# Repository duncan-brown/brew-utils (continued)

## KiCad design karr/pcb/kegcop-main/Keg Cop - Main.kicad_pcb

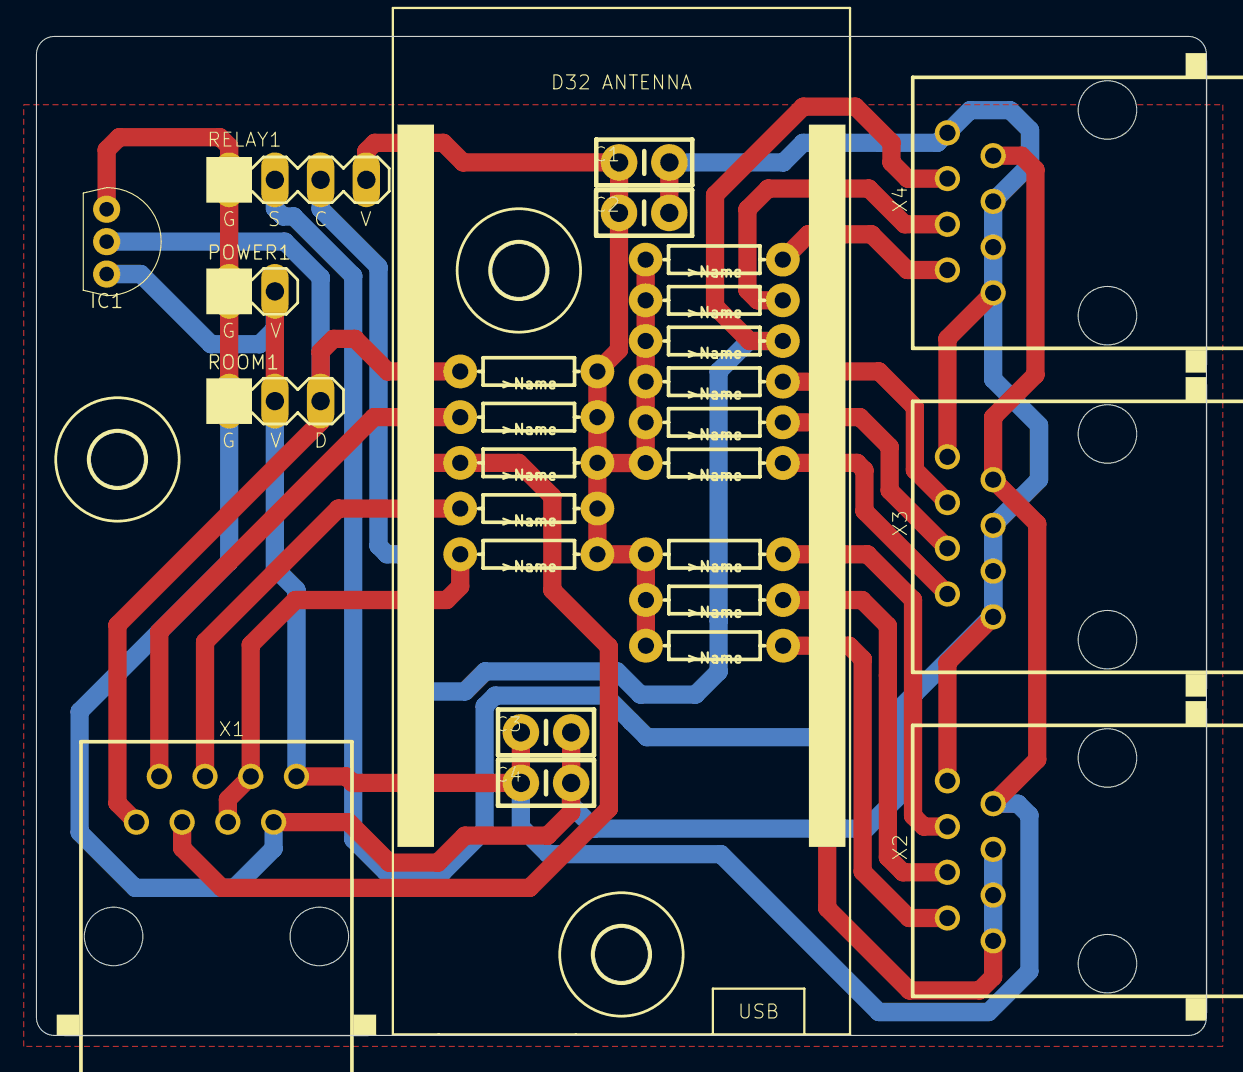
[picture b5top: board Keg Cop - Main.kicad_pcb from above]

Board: 2 copper layers, 65.0 x 55.5 mm, 30 parts (0 on the bottom side), 19 nets.

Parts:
C1, C3: 0.1μF; CAP_PTH-2.54
C2, C4: 1.0μF; CAP_PTH-2.54
D32: Lolin D32; D32_NO_BATT
IC1: DS18B20+; TO-92
POWER1: 2-PIN; HDR-2_VERT
R1, R2, R3, R4, R5, R6, R7, R8, R9, R10, R11, R12, R13, R14: 2.2kΩ; AXIAL-0.3
RELAY1: 4-PIN; MA04-1
ROOM1: 3-PIN; HDR-3_VERT
U$1, U$2, U$3: 3,0
X1, X2, X3, X4: RJ45; RJ45-NO-SHIELD

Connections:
/3V3: C1.1, C2.1, D32.VCC, R1.P$1, R2.P$1, R3.P$1, R4.P$1, R5.P$1, R6.P$2, R7.P$2, R8.P$2, R9.P$2, R10.P$2, R11.P$2, R12.P$2, R13.P$2, R14.P$2, RELAY1.4
/5V: C3.1, C4.1, D32.VBUS, IC1.3, POWER1.2, ROOM1.2, X1.8, X2.7, X3.7, X4.7
/COOL: D32.IO27, RELAY1.3
/GND: C1.2, C2.2, C3.2, C4.2, D32.GND, D32.GND2, IC1.1, POWER1.1, RELAY1.1, ROOM1.1, X1.7, X2.1, X2.3, X2.5, X2.8, X3.1, X3.3, X3.5, X3.8, X4.1, X4.3, X4.5, X4.8
/KDAT: D32.IO14, R5.P$2, X1.5, X1.6
/KEG0: D32.IO4, R14.P$1, X2.2
/KEG1: D32.IO16, R13.P$1, X2.4
/KEG2: D32.IO17, R12.P$1, X2.6
/KEG3: D32.IO18, R11.P$1, X3.2
/KEG4: D32.IO19, R10.P$1, X3.4
/KEG5: D32.IO21, R9.P$1, X3.6
/KEG6: D32.IO22, R8.P$1, X4.2
/KEG7: D32.IO23, R7.P$1, X4.4
/KEG8: D32.IO13, R6.P$1, X4.6
/LDAT: D32.IO26, R4.P$2, X1.4
/RDAT: D32.IO32, IC1.2, R1.P$2, ROOM1.3, X1.1
/SOL: D32.IO2, RELAY1.2
/TDAT: D32.IO33, R2.P$2, X1.2
/UDAT: D32.IO25, R3.P$2, X1.3

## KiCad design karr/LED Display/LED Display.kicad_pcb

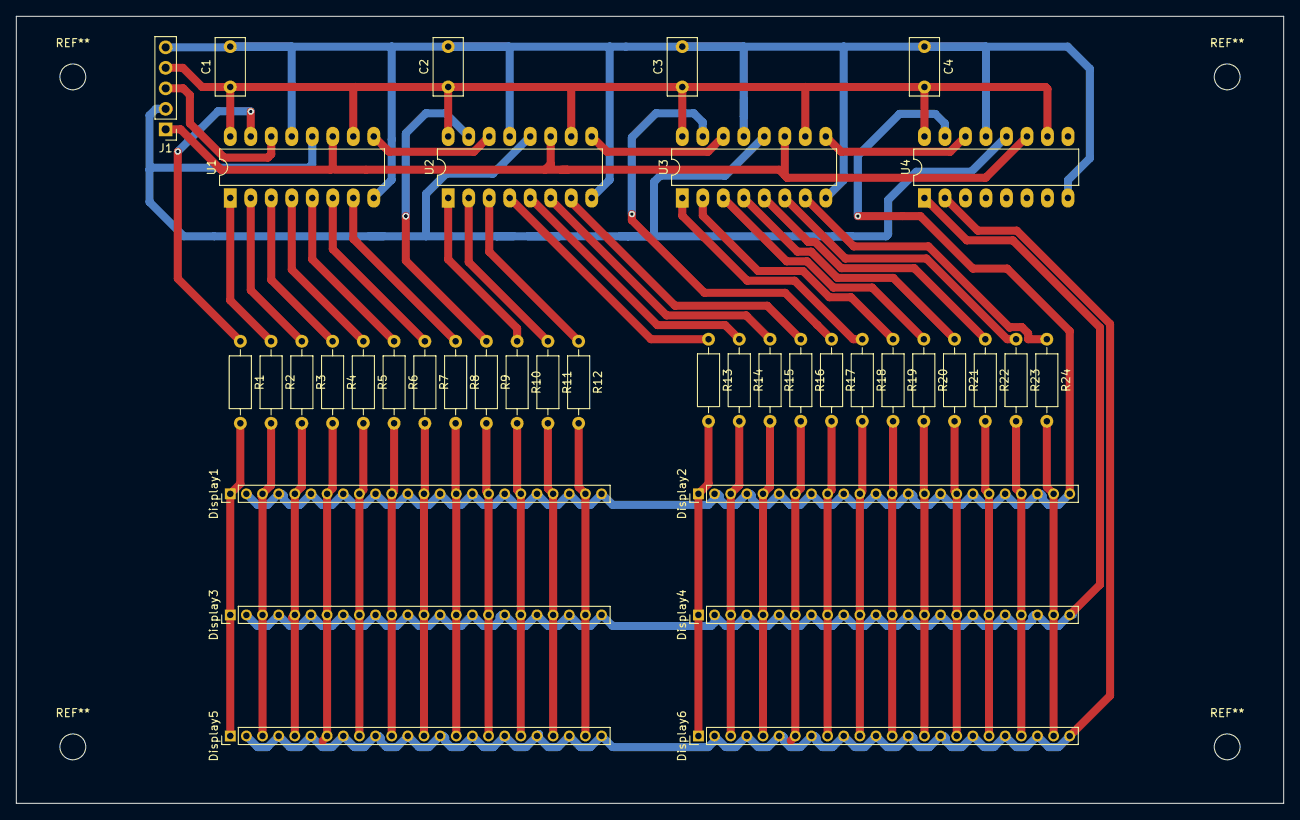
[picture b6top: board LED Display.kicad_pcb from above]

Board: 2 copper layers, 157.0 x 97.5 mm, 39 parts (0 on the bottom side), 59 nets.

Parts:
C1, C2, C3, C4: 100nF; C_Rect_L7.0mm_W3.5mm_P5.00mm
Display1, Display3, Display5: STBD001-4R8G; PinHeader_1x24_P2.00mm_Vertical
Display2, Display4, Display6: KYX-125807R; PinHeader_1x24_P2.00mm_Vertical
J1: Conn_01x05; PinHeader_1x05_P2.54mm_Vertical
R1, R2, R3, R4, R13, R14, R15, R16, R17, R18, R19, R20, R21, R22, R23, R24: 2k2; R_Axial_DIN0207_L6.3mm_D2.5mm_P10.16mm_Horizontal
R5, R6, R7, R8, R9, R10, R11, R12: 680R; R_Axial_DIN0207_L6.3mm_D2.5mm_P10.16mm_Horizontal
U1, U2, U3, U4: 74HC595; DIP-16_W7.62mm_LongPads

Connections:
+5V: C1.1, C2.1, C3.1, C4.2, J1.4, U1.10, U1.16, U2.10, U2.16, U3.10, U3.16, U4.10, U4.16
GND: C1.2, C2.2, C3.2, C4.1, J1.5, U1.8, U1.13, U2.8, U2.13, U3.8, U3.13, U4.8, U4.13
unnamed: Display1.1, Display3.1, Display5.1, R1.2
unnamed: Display1.3, Display3.3, Display5.3, R2.2
unnamed: Display1.5, Display3.5, Display5.5, R3.2
unnamed: Display1.7, Display3.7, Display5.7, R4.2
unnamed: Display1.9, Display3.9, Display5.9, R5.2
unnamed: Display1.2, Display1.4, Display1.6, Display1.8, Display1.10, Display1.12, Display1.14, Display1.16, Display1.18, Display1.20, Display1.22, Display1.24, Display2.2, Display2.4, Display2.6, Display2.8, Display2.10, Display2.12, Display2.14, Display2.16, Display2.18, Display2.20, Display2.22, Display2.24, U4.15
unnamed: Display1.11, Display3.11, Display5.11, R6.2
unnamed: Display1.13, Display3.13, Display5.13, R7.2
unnamed: Display1.15, Display3.15, Display5.15, R8.2
unnamed: Display1.17, Display3.17, Display5.17, R9.2
unnamed: Display1.19, Display3.19, Display5.19, R10.2
unnamed: Display1.21, Display3.21, Display5.21, R11.2
unnamed: Display1.23, Display3.23, Display5.23, R12.2
unnamed: Display2.1, Display4.1, Display6.1, R13.2
unnamed: Display2.3, Display4.3, Display6.3, R14.2
unnamed: Display2.5, Display4.5, Display6.5, R15.2
unnamed: Display2.7, Display4.7, Display6.7, R16.2
unnamed: Display2.9, Display4.9, Display6.9, R17.2
unnamed: Display2.11, Display4.11, Display6.11, R18.2
unnamed: Display2.13, Display4.13, Display6.13, R19.2
unnamed: Display2.15, Display4.15, Display6.15, R20.2
unnamed: Display2.17, Display4.17, Display6.17, R21.2
unnamed: Display2.19, Display4.19, Display6.19, R22.2
unnamed: Display2.21, Display4.21, Display6.21, R23.2
unnamed: Display2.23, Display4.23, Display6.23, R24.2
unnamed: Display3.2, Display3.4, Display3.6, Display3.8, Display3.10, Display3.12, Display3.14, Display3.16, Display3.18, Display3.20, Display3.22, Display3.24, Display4.2, Display4.4, Display4.6, Display4.8, Display4.10, Display4.12, Display4.14, Display4.16, Display4.18, Display4.20, Display4.22, Display4.24, U4.1
unnamed: Display5.2, Display5.4, Display5.6, Display5.8, Display5.10, Display5.12, Display5.14, Display5.16, Display5.18, Display5.20, Display5.22, Display5.24, Display6.2, Display6.4, Display6.6, Display6.8, Display6.10, Display6.12, Display6.14, Display6.16, Display6.18, Display6.20, Display6.22, Display6.24, U4.2
unnamed: J1.1, U1.11, U2.11, U3.11, U4.11
unnamed: J1.2, U1.12, U2.12, U3.12, U4.12
unnamed: J1.3, U1.14
unnamed: R1.1, U1.15
unnamed: R2.1, U1.1
unnamed: R3.1, U1.2
unnamed: R4.1, U1.3
unnamed: R5.1, U1.4
unnamed: R6.1, U1.5
unnamed: R7.1, U1.6
unnamed: R8.1, U1.7
unnamed: R9.1, U2.15
unnamed: R10.1, U2.1
unnamed: R11.1, U2.2
unnamed: R12.1, U2.3
unnamed: R13.1, U2.4
unnamed: R14.1, U2.5
unnamed: R15.1, U2.6
unnamed: R16.1, U2.7
unnamed: R17.1, U3.15
unnamed: R18.1, U3.1
unnamed: R19.1, U3.2
unnamed: R20.1, U3.3
unnamed: R21.1, U3.4
unnamed: R22.1, U3.5
unnamed: R23.1, U3.6
unnamed: R24.1, U3.7
unnamed: U1.9, U2.14
unnamed: U2.9, U3.14
unnamed: U3.9, U4.14

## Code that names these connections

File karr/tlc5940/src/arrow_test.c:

#include <stdio.h>
#include <stdlib.h>
#include <string.h>

#include "arrow_test.h"

#include "freertos/FreeRTOS.h"
#include "freertos/task.h"
#include "esp_err.h"
#include "esp_log.h"

#include "st7789.h"
#include "fontx.h"

extern uint16_t segment_0;
extern uint16_t bar;

TickType_t DisplaySegment0(TFT_t * dev, FontxFile *fx, int width, int height) {
	TickType_t startTick, endTick, diffTick;
	startTick = xTaskGetTickCount();

	// get font width & height
	uint8_t buffer[FontxGlyphBufSize];
	uint8_t fontWidth;
	uint8_t fontHeight;
	GetFontx(fx, 0, buffer, &fontWidth, &fontHeight);
	//ESP_LOGI(__FUNCTION__,"fontWidth=%d fontHeight=%d",fontWidth,fontHeight);
	
	uint16_t xpos;
	uint16_t ypos;
	const uint8_t ascii_len = 28;
	uint8_t ascii[ascii_len];
	uint16_t color;

	lcdFillScreen(dev, BLACK);
	lcdSetFontDirection(dev, DIRECTION90);
	color = WHITE;
	ypos = 0;
    xpos = width - 1;

    snprintf((char *)ascii, ascii_len, "%d (%d)", segment_0, bar);
	xpos -= fontHeight + 1;
	lcdDrawString(dev, fx, xpos, ypos, ascii, color);

	endTick = xTaskGetTickCount();
	diffTick = endTick - startTick;
	ESP_LOGI(__FUNCTION__, "elapsed time[ms]:%d",diffTick*portTICK_RATE_MS);
	return diffTick;
}

TickType_t DisplayTLCPins(TFT_t * dev, FontxFile *fx, int width, int height) {
	TickType_t startTick, endTick, diffTick;
	startTick = xTaskGetTickCount();

	// get font width & height
	uint8_t buffer[FontxGlyphBufSize];
	uint8_t fontWidth;
	uint8_t fontHeight;
	GetFontx(fx, 0, buffer, &fontWidth, &fontHeight);
	//ESP_LOGI(__FUNCTION__,"fontWidth=%d fontHeight=%d",fontWidth,fontHeight);
	
	uint16_t xpos;
	uint16_t ypos;
	const uint8_t ascii_len = 28;
	uint8_t ascii[ascii_len];
	uint16_t color;

	lcdFillScreen(dev, BLACK);
	lcdSetFontDirection(dev, DIRECTION90);
	color = WHITE;
	ypos = 0;
    xpos = width - 1;

    snprintf((char *)ascii, ascii_len, "    SIN: %d   VPRG: %d", CONFIG_TLC_SIN_PIN, CONFIG_TLC_VPRG_PIN);
	xpos -= fontHeight + 1;
	lcdDrawString(dev, fx, xpos, ypos, ascii, color);

	snprintf((char *)ascii, ascii_len, "   SOUT: %d   XLAT: %d", CONFIG_TLC_SOUT_PIN, CONFIG_TLC_XLAT_PIN);
	xpos -= fontHeight + 1;
	lcdDrawString(dev, fx, xpos, ypos, ascii, color);

	snprintf((char *)ascii, ascii_len, "   SCLK: %d  BLANK: %d", CONFIG_TLC_SCLK_PIN, CONFIG_TLC_BLANK_PIN);
	xpos -= fontHeight + 1;
	lcdDrawString(dev, fx, xpos, ypos, ascii, color);

	snprintf((char *)ascii, ascii_len, "  DCPRG: %d  GSCLK: %d", CONFIG_TLC_DCPRG_PIN, CONFIG_TLC_GSCLK_PIN);
	xpos -= fontHeight + 1;
	lcdDrawString(dev, fx, xpos, ypos, ascii, color);

	snprintf((char *)ascii, ascii_len, "COUNTER: %d  LINE 1: %d", CONFIG_TLC_COUNTER_PIN, CONFIG_TLC_LINE_1_PIN);
	xpos -= fontHeight + 1;
	lcdDrawString(dev, fx, xpos, ypos, ascii, color);

	snprintf((char *)ascii, ascii_len, "  LINE2: %d  LINE 3: %d", CONFIG_TLC_LINE_2_PIN, CONFIG_TLC_LINE_3_PIN);
	xpos -= fontHeight + 1;
	lcdDrawString(dev, fx, xpos, ypos, ascii, color);

	endTick = xTaskGetTickCount();
	diffTick = endTick - startTick;
	ESP_LOGI(__FUNCTION__, "elapsed time[ms]:%d",diffTick*portTICK_RATE_MS);
	return diffTick;
}

TickType_t ArrowTest(TFT_t * dev, FontxFile *fx, int width, int height) {
	TickType_t startTick, endTick, diffTick;
	startTick = xTaskGetTickCount();

	// get font width & height
	uint8_t buffer[FontxGlyphBufSize];
	uint8_t fontWidth;
	uint8_t fontHeight;
	GetFontx(fx, 0, buffer, &fontWidth, &fontHeight);
	//ESP_LOGI(__FUNCTION__,"fontWidth=%d fontHeight=%d",fontWidth,fontHeight);
	
	uint16_t xpos;
	uint16_t ypos;
	int	stlen;
	uint8_t ascii[24];
	uint16_t color;

	lcdFillScreen(dev, BLACK);

	strcpy((char *)ascii, "KARR");
	if (width < height) {
		xpos = ((width - fontHeight) / 2) - 1;
		ypos = (height - (strlen((char *)ascii) * fontWidth)) / 2;
		lcdSetFontDirection(dev, DIRECTION90);
	} else {
		ypos = ((height - fontHeight) / 2) - 1;
		xpos = (width - (strlen((char *)ascii) * fontWidth)) / 2;
		lcdSetFontDirection(dev, DIRECTION0);
	}
	color = WHITE;
	lcdDrawString(dev, fx, xpos, ypos, ascii, color);

	lcdSetFontDirection(dev, 0);
	color = RED;
	lcdDrawFillArrow(dev, 10, 10, 0, 0, 5, color);
	strcpy((char *)ascii, "0,0");
	lcdDrawString(dev, fx, 0, 30, ascii, color);

	color = GREEN;
	lcdDrawFillArrow(dev, width-11, 10, width-1, 0, 5, color);
	//strcpy((char *)ascii, "79,0");
	sprintf((char *)ascii, "%d,0",width-1);
	stlen = strlen((char *)ascii);
	xpos = (width-1) - (fontWidth*stlen);
	lcdDrawString(dev, fx, xpos, 30, ascii, color);

	color = GRAY;
	lcdDrawFillArrow(dev, 10, height-11, 0, height-1, 5, color);
	//strcpy((char *)ascii, "0,159");
	sprintf((char *)ascii, "0,%d",height-1);
	ypos = (height-11) - (fontHeight) + 5;
	lcdDrawString(dev, fx, 0, ypos, ascii, color);

	color = CYAN;
	lcdDrawFillArrow(dev, width-11, height-11, width-1, height-1, 5, color);
	//strcpy((char *)ascii, "79,159");
	sprintf((char *)ascii, "%d,%d",width-1, height-1);
	stlen = strlen((char *)ascii);
	xpos = (width-1) - (fontWidth*stlen);
	lcdDrawString(dev, fx, xpos, ypos, ascii, color);

	endTick = xTaskGetTickCount();
	diffTick = endTick - startTick;
	ESP_LOGI(__FUNCTION__, "elapsed time[ms]:%d",diffTick*portTICK_RATE_MS);
	return diffTick;
}

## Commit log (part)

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2020-08-01 cvs conversion program
2021-02-15 test program for 7-segment led
2021-02-16 fixed for correct segment pinout
2021-02-16 fixed loop
2021-02-16 include 9
2021-02-16 set all digits
2021-02-16 set ground pins and fix indentation
2021-02-16 update ground pins
2021-02-16 reduce flicker and break out digits
2021-02-16 move 20->16, 16->12
2021-02-16 don't blink dp
2021-02-16 reduce flicker
2021-02-16 removed redundant modulo test
2021-02-17 set up for low side switches
2021-02-17 test program using pigpen library
2021-02-17 pigpio based version
2021-02-17 decrease flicker
2021-02-17 add mash temp
2021-02-17 start mash temp thread
2021-02-17 fix mash probe name
2021-02-17 mash temp is a float
2021-02-17 remove decimal point from temp string
2021-02-17 fix mash temp formatting
2021-02-17 fix 6
2021-02-17 systemd service file
2021-02-19 update probe names for two buses
2021-02-19 update mash probe id
2021-02-20 remove duplicate import
2021-02-20 simple program to print temperature and time
2021-02-20 print time in minutes
2021-02-27 try to fix crash
    https://raspberrypi.stackexchange.com/questions/61621/sending-new-wave-to-pigpiod-causes-pi-to-lock-up
2021-02-28 avoid crash and blink
2021-02-28 fix typo
2021-03-14 added kicad files for led display
2021-04-11 add all 6 keezer probes
2021-07-24 rewire pins
2021-07-24 rewire again
2021-07-24 add hlt probe
2021-07-24 typo
2021-07-24 update probe ids
2021-08-06 rename prototypes
2021-08-06 original version from lbussy
2021-08-06 initial entry
2021-08-06 group outline
2021-08-07 inital entry
2021-08-07 removed pdf
2021-08-08 https://github.com/Xinyuan-LilyGO/TTGO-T-Display/issues/28#issuecomment-619570440
2021-08-08 switch to https://github.com/BravoRoot/ttgo-tdisplay-kicad
2021-08-08 from https://github.com/BravoRoot/ttgo-tdisplay-kicad
2021-08-08 ttgo plus seven chips
2021-08-08 based on mph
2021-08-08 fixed labels
2021-08-08 removed old file
2021-08-08 cloned with https://github.com/bobc/KiRename
2021-08-08 first four 7-segment displays
2021-08-08 store all libraries in project
2021-08-08 wire up a-f on displays
2021-08-08 created footpad for 7-segment
2021-08-08 added symbols
2021-08-08 fixed footpads
2021-08-08 add coupling capacitors
2021-08-08 fixed missing footpads
2021-08-08 added datasheets
2021-08-08 switch regulator
2021-08-08 finished wiring
2021-08-08 reworked pins
2021-08-08 added mph leds
2021-08-08 added title
2021-08-08 added author
2021-08-08 added msg tx
2021-08-09 add blanking resistors
2021-08-09 copied custom symbols
2021-08-09 check libs
2021-08-09 http://www.mosaic-industries.com/embedded-systems/microcontroller-projects/raspberry-pi/on-off-power-controller
2021-08-09 add data sheets
2021-08-12 removed old copies
2021-08-12 fixed typo
2021-08-12 add 12 segment bars
2021-08-12 initial wiring
2021-08-12 fixed ttgo
2021-08-12 finished initial wiring
2021-08-12 fixed for bug checker
2021-08-12 duplicated left side
2021-08-12 added right bar displays
2021-08-12 finished wiring and bug check
2021-08-12 removed temporary file
2021-08-12 add libraries
2021-08-12 created lower pcb and bug check
2021-08-12 fixed colors on bar displays
2021-08-12 fixed lib references
2021-08-12 fixed red and green bars
2021-08-17 add flangeless led footprint
2021-08-17 sed to get flangeless led
2021-08-17 add led footprints
2021-08-17 added screw terminals
2021-08-17 added footpads for light blocks and screw terminals
2021-08-17 datasheets for 12 seg leds
2021-08-18 add footpad for 12 seg leds
2021-08-18 add 12 seg led footprints
2021-08-18 added footpads
2021-08-18 add footpad for logic level shifter
2021-08-18 add logic level shifter
2021-08-18 pcb outline
2021-08-19 prototype layout
2021-08-19 add pegboard holes
2021-08-19 removed dummy components
2021-08-19 changed pegboard holes to m5
2021-08-19 initial placement
2021-08-19 initial netlist
2021-08-19 finished placing leds
2021-08-19 place chips and resistors
2021-08-19 add net ties for coupling caps
2021-08-19 routed led display chips
2021-08-19 finshed mph placement
2021-08-19 fill zones
2021-08-20 more wiring
2021-08-20 finished wiring mph
2021-08-20 drc check
2021-08-20 rpm curve
2021-08-20 fixed coupling caps and blank resistors
2021-08-20 fixed pegboard to 25mm spacing
2021-08-20 fixed pegboard spacing
2021-08-20 placed rpm leds
2021-08-20 added extra cg led
2021-08-20 reworked rpm leds
2021-08-20 moved back from print position
2021-08-20 reposition based on printout
2021-08-20 check and measured rpm leds
2021-08-21 individual footpads for 12 segs
2021-08-21 fixed 12 seg leds
2021-08-21 220 tab down
2021-08-21 add datasheet
2021-08-21 switch yellow leds to mosfets
2021-08-22 changed for new optoelectronics
2021-08-22 get rid of some vias
2021-08-22 label components
2021-08-22 update lvl footprint
2021-08-24 fixed footprints for mph leds
2021-08-24 ttgo hello world
2021-08-24 test text
2021-08-25 added air oil s and p
2021-08-29 moved to prototypes
2021-08-29 test program to blink digital pin
2021-08-29 add font and image files
2021-08-29 add spiffs partition map
2021-08-29 created by platformio
2021-08-29 add src from upstream
2021-08-29 ran menuconfig
2021-08-29 added speeds
2021-08-29 copied from st7789
2021-08-29 removed latin font
2021-08-29 removed extraneous files
2021-08-29 defaults for ttgo t-display
2021-08-29 added tlc5940 pins
2021-08-29 removed unused file
2021-09-06 update pins
2021-09-06 add tlc5940.c
2021-09-06 set and display tlc pins
2021-09-06 change spis
2021-09-06 add more code
2021-09-06 fixed compile
2021-09-06 working prototype of lcd
2021-09-06 change to gpio pins
2021-09-07 reduce interval and fix headers
2021-09-08 smaller font
2021-09-09 drive 12 segment led bar
2023-02-21 igore apple file
2023-02-21 add conversion script
2023-02-21 update vscode
2023-04-13 moved prototype code
2023-04-13 inital version of panp scripts
2023-04-14 enable panp lamps
2023-04-14 control panp buttons
2023-04-14 start earlier but after serial
2023-04-15 control dash lights
2023-04-15 communicate auto mode on gpio 16->6
2023-04-15 shut down dash on exit
2023-04-23 enable serial converter
2023-04-23 new relays
2023-04-23 fixed lamps on boot
2023-04-23 fixed power on boot
2023-04-23 set brightness based on norm/pursuit
2023-04-23 display temperatures on brewpi
2023-04-23 handle brightness for all displays
2023-04-23 reduce brightness
2023-04-26 clean exit
2023-04-27 use thread primitive
2023-04-28 better handling of serial comms
2023-04-29 set ports correctly
2023-04-29 open power relay on brewpi
2023-04-29 fixed incorrect variable name and function call
2023-04-29 notify on sigint
2023-04-29 display keezer temps
2023-04-29 add git ignore file
2023-04-29 switchpod processing from paolo
2023-04-29 add switchpod handling
2023-04-29 handle switchpod commands
2023-04-30 better exit handling
2023-04-30 fix handling of switchpod
2023-04-30 more generous timing on dim
2023-04-30 handle power relay separately
2023-04-30 list ports on separate lines
2023-04-30 fix race condition
2023-04-30 abstract temp probe get
2023-04-30 reduce sleep time
2023-04-30 change leds
2023-04-30 set buttons immediately
2023-04-30 thread to get hot side temps
2023-04-30 set msg ctr based on key press
2023-04-30 display brewpi temperature on switchpod presses
2023-04-30 use same variable for normal_mode_comm
2023-04-30 make loops more robust
2023-04-30 smaller wait time
2023-04-30 do not update displays in auto mode
2023-04-30 add sleeps
2023-04-30 shorter startup sleep
2023-04-30 show temps on fermenter bars
2023-05-01 show keg status on dummy6 and dummy3
2023-05-01 round upper temp
2023-05-01 sleeps
2023-05-01 rotating log message with status
2023-05-02 fixed rotating display
2023-05-06 added lager probes
2023-05-06 fixed 50 on circle
2023-05-21 switched lager probe two
2023-05-28 only update fermenter state every five mins
2023-05-28 update fermenter state every minute
2023-05-29 setup flowmeter pins
2023-07-23 display lager on rpm
2023-07-23 fixed off by one error
2024-03-02 control flowmeter relays
2024-03-03 fixed left switchpod
2024-03-03 restart switchpod on error
2024-03-10 tweak brightness
2025-02-09 fix red/green dummy 3
2025-02-22 retry clear of red/green dummy3
2025-03-07 more robust display
2025-03-09 tweak red/green fermenter temps
